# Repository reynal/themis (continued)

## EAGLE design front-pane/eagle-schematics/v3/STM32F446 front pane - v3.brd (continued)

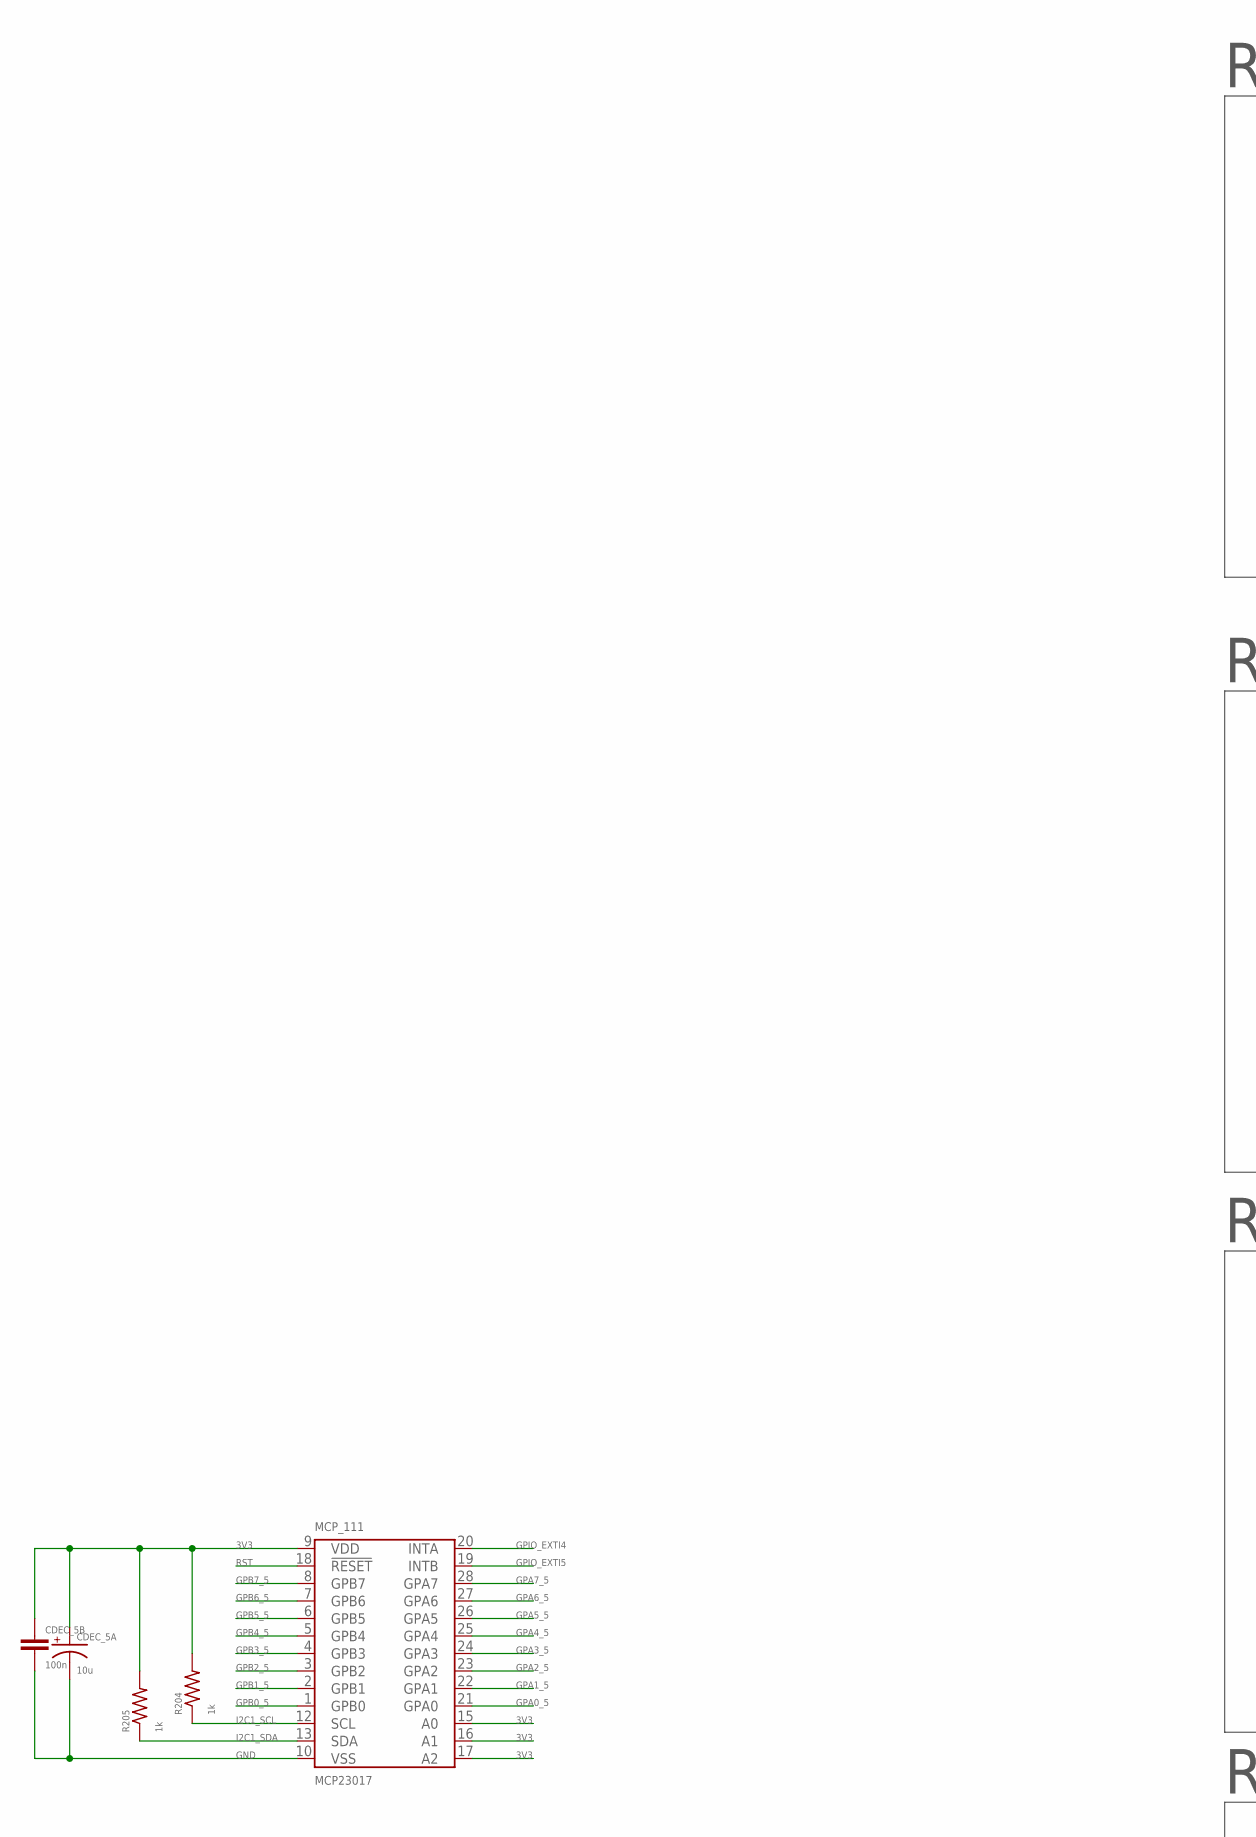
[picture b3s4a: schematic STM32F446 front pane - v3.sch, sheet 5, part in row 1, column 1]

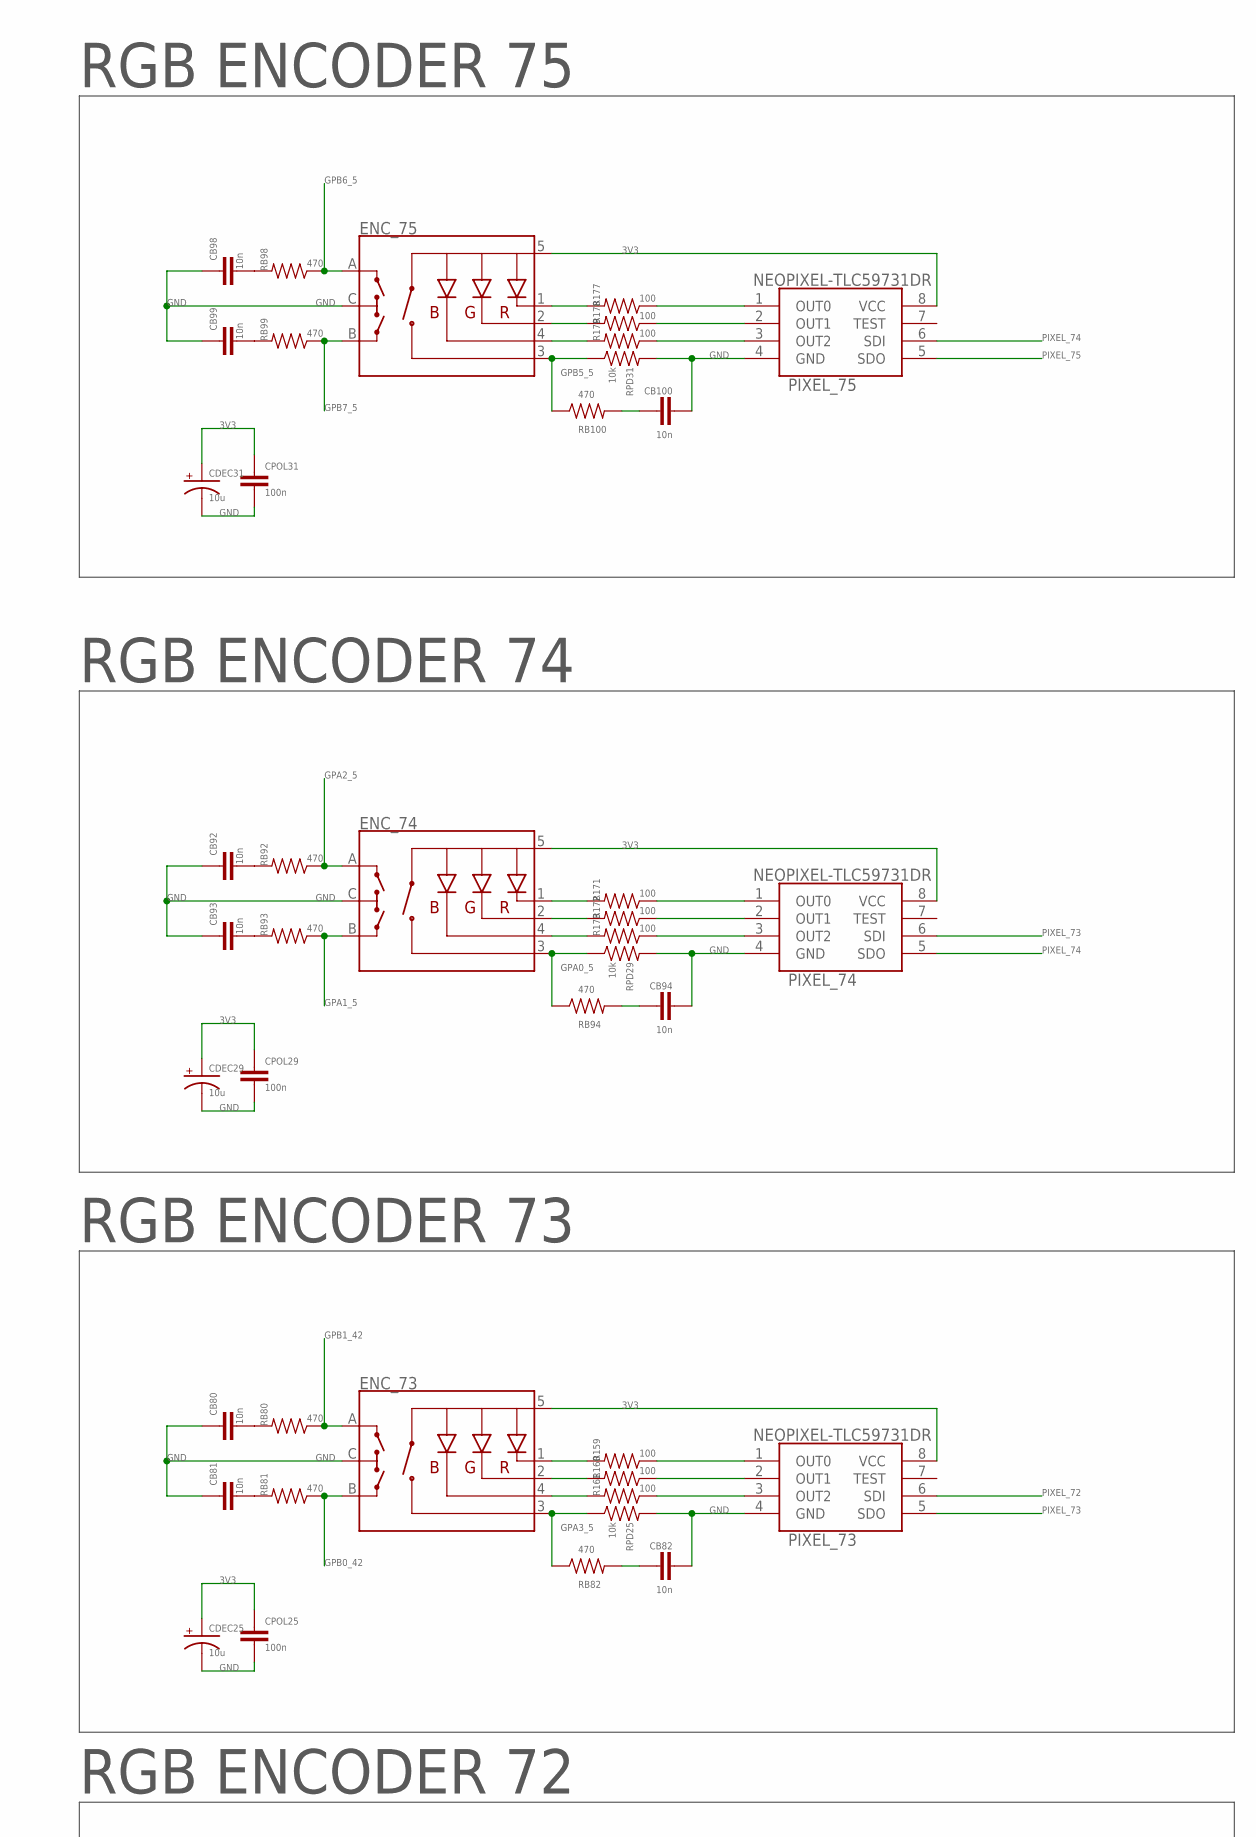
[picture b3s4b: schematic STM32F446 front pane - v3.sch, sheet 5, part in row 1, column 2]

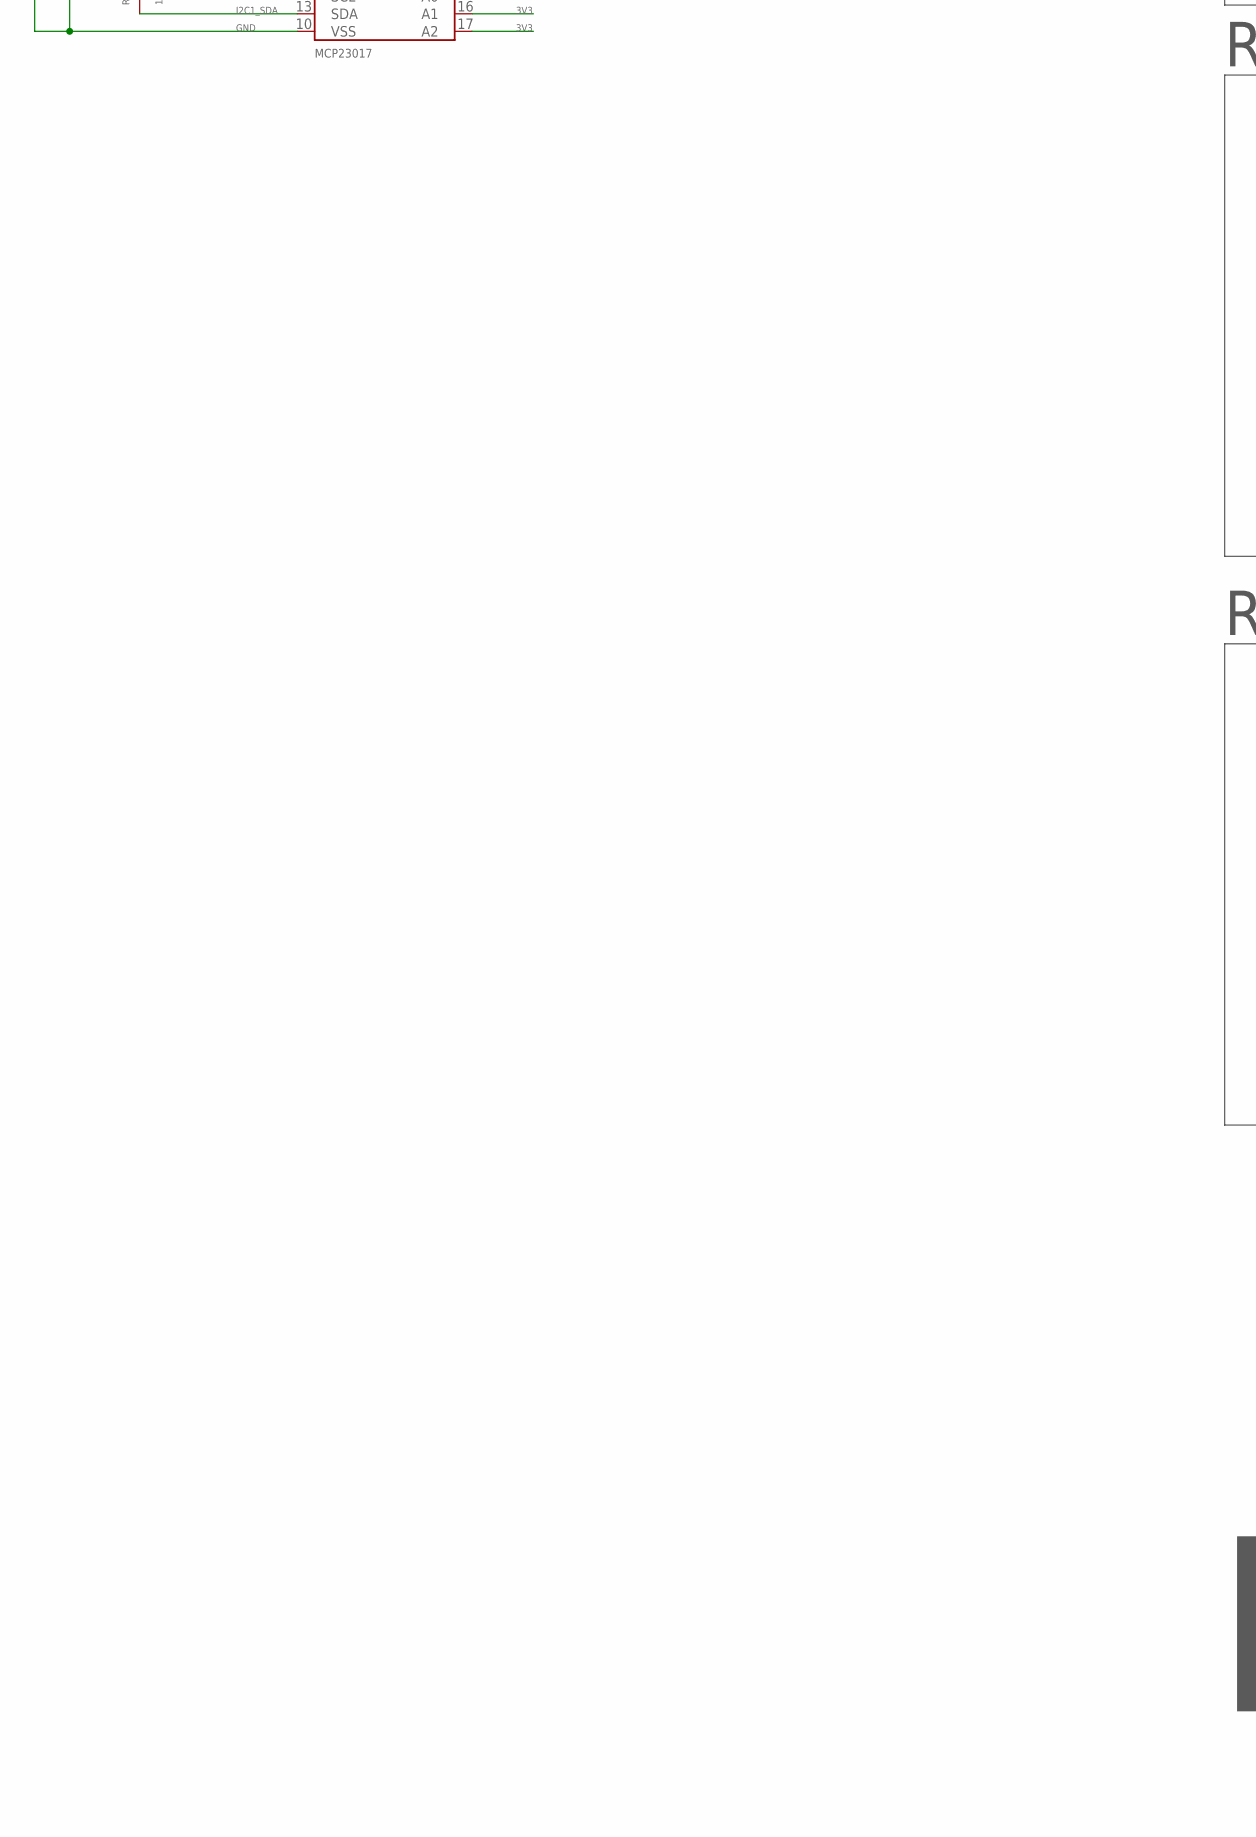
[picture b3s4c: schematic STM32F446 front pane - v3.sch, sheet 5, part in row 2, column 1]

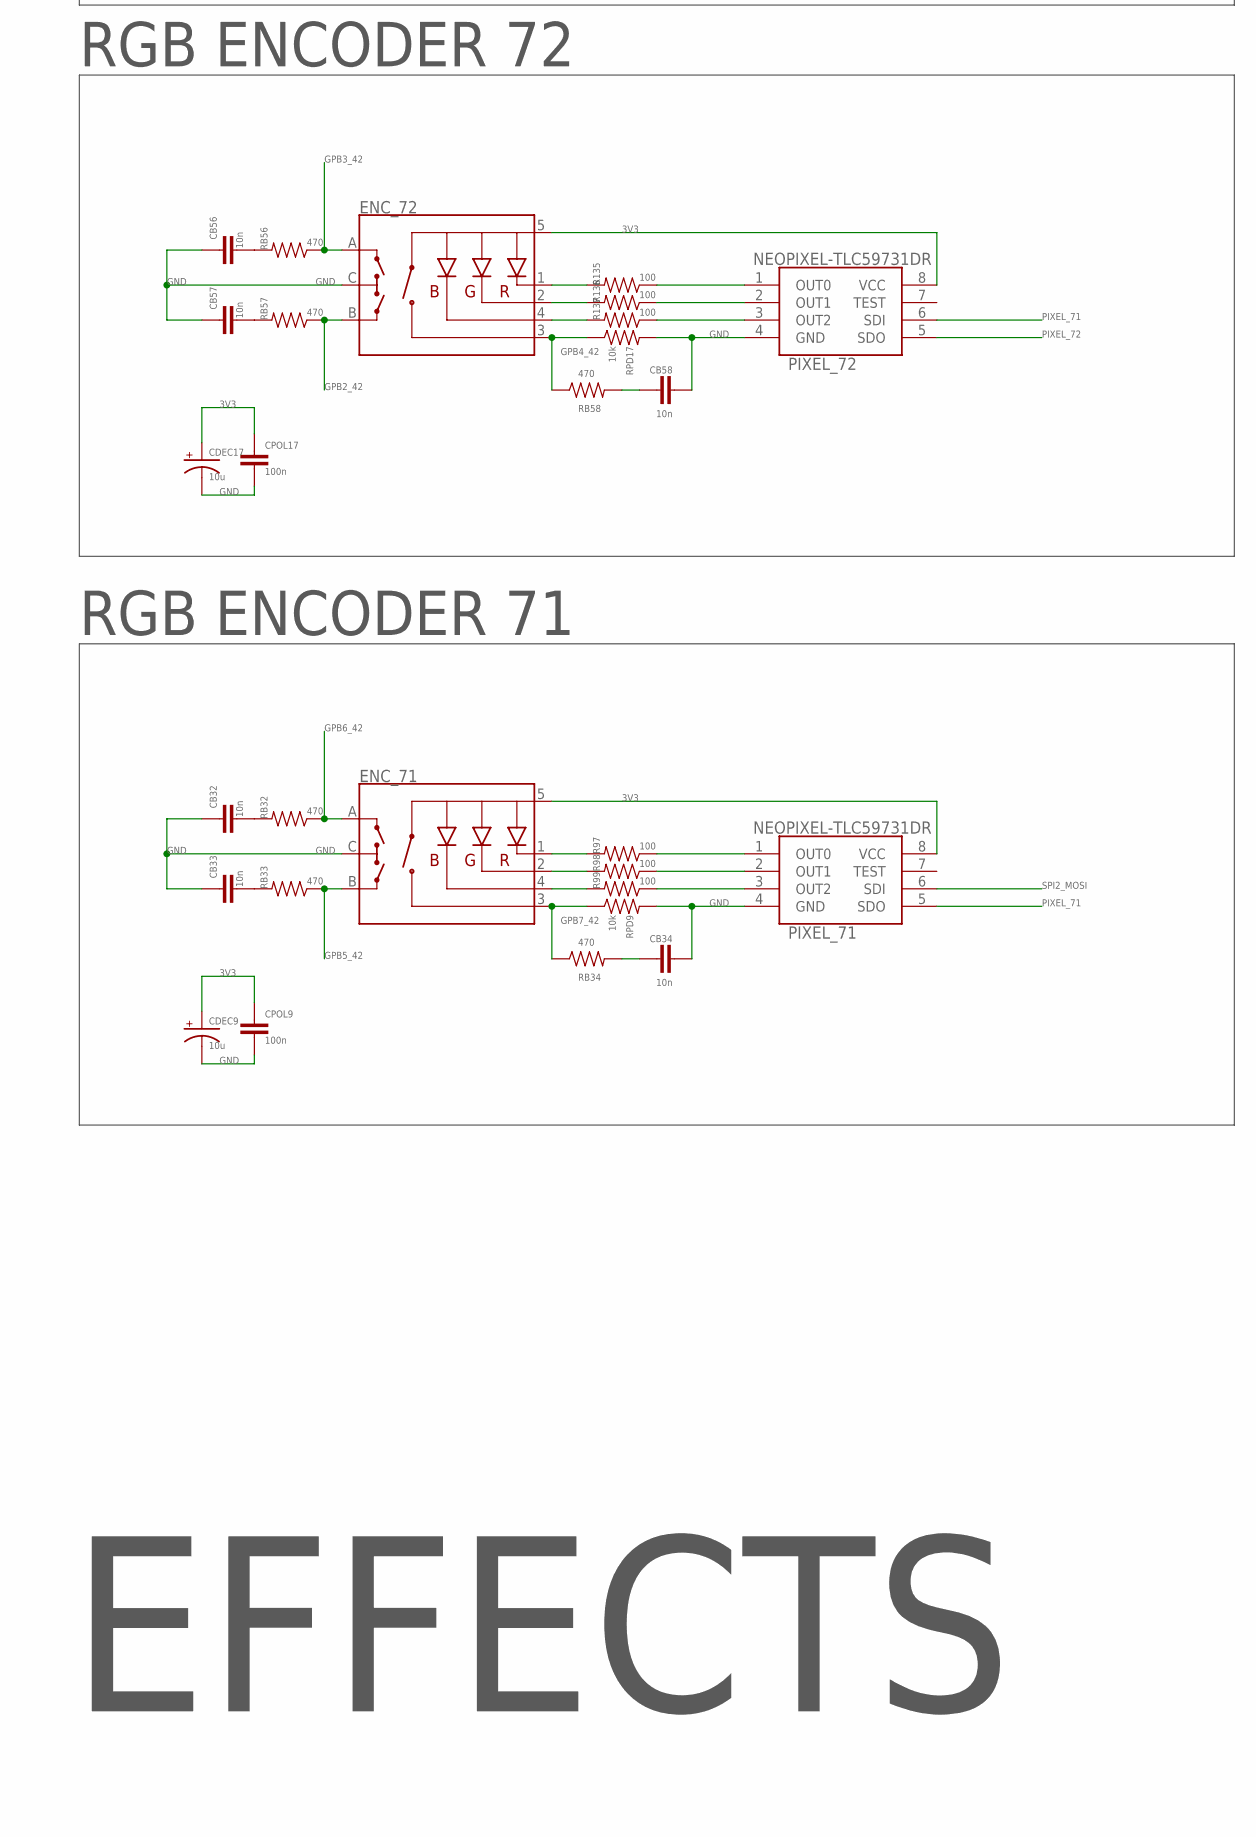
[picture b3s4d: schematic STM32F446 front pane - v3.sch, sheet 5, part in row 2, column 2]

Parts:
CB32, CB33, CB34, CB56, CB57, CB58, CB80, CB81, CB82, CB92, CB93, CB94, CB98, CB99, CB100: 10n; 0805-CAP
CDEC9, CDEC17, CDEC25, CDEC29, CDEC31: 10u; CPOL2917
CDEC_5A: 10u; CPOL2917
CDEC_5B: 100n; 0805-CAP
CPOL9, CPOL17, CPOL25, CPOL29, CPOL31: 100n; 0805-CAP
ENC_71, ENC_72, ENC_73, ENC_74, ENC_75: ENCODER-RGB-SWITCH-NO_NUT; ENCODER_LED_3
MCP_111: MCP23017; SOIC-28
PIXEL_71, PIXEL_72, PIXEL_73, PIXEL_74, PIXEL_75: NEOPIXEL-TLC59731DR; SOIC127P600X175-8N
R97, R98, R99, R135, R136, R137, R159, R160, R161, R171, R172, R173, R177, R178, R179: 100; 1206
R204, R205: 1k; R0805
RB32, RB33, RB34, RB56, RB57, RB58, RB80, RB81, RB82, RB92, RB93, RB94, RB98, RB99, RB100: 470; 1206
RPD9, RPD17, RPD25, RPD29, RPD31: 10k; 1206

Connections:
3V3: CDEC9.+, CDEC17.+, CDEC25.+, CDEC29.+, CDEC31.+, CDEC_5A.+, CDEC_5B.1, CPOL9.1, CPOL17.1, CPOL25.1, CPOL29.1, CPOL31.1, ENC_71.5 (+), ENC_72.5 (+), ENC_73.5 (+), ENC_74.5 (+), ENC_75.5 (+), MCP_111.9 (VDD), MCP_111.15 (A0), MCP_111.16 (A1), MCP_111.17 (A2), PIXEL_71.8 (VCC), PIXEL_72.8 (VCC), PIXEL_73.8 (VCC), PIXEL_74.8 (VCC), PIXEL_75.8 (VCC), R204.2, R205.2; also elsewhere on the board
GND: CB32.1, CB33.1, CB34.2, CB56.1, CB57.1, CB58.2, CB80.1, CB81.1, CB82.2, CB92.1, CB93.1, CB94.2, CB98.1, CB99.1, CB100.2, CDEC9.-, CDEC17.-, CDEC25.-, CDEC29.-, CDEC31.-, CDEC_5A.-, CDEC_5B.2, CPOL9.2, CPOL17.2, CPOL25.2, CPOL29.2, CPOL31.2, ENC_71.C, ENC_72.C, ENC_73.C, ENC_74.C, ENC_75.C, MCP_111.10 (VSS), PIXEL_71.4 (GND), PIXEL_72.4 (GND), PIXEL_73.4 (GND), PIXEL_74.4 (GND), PIXEL_75.4 (GND), RPD9.2, RPD17.2, RPD25.2, RPD29.2, RPD31.2; also elsewhere on the board
GPA0_5: ENC_74.3 (SW), MCP_111.21 (GPA0), RB94.1, RPD29.1
GPA1_5: ENC_74.B, MCP_111.22 (GPA1), RB93.1
GPA2_5: ENC_74.A, MCP_111.23 (GPA2), RB92.1
GPA3_5: ENC_73.3 (SW), MCP_111.24 (GPA3), RB82.1, RPD25.1
GPA4_5: MCP_111.25 (GPA4); also elsewhere on the board
GPA5_5: MCP_111.26 (GPA5); also elsewhere on the board
GPA6_5: MCP_111.27 (GPA6); also elsewhere on the board
GPA7_5: MCP_111.28 (GPA7); also elsewhere on the board
GPB0_5: MCP_111.1 (GPB0); also elsewhere on the board
GPB0_42: ENC_73.B, RB81.1; also elsewhere on the board
GPB1_5: MCP_111.2 (GPB1); also elsewhere on the board
GPB1_42: ENC_73.A, RB80.1; also elsewhere on the board
GPB2_5: MCP_111.3 (GPB2); also elsewhere on the board
GPB2_42: ENC_72.B, RB57.1; also elsewhere on the board
GPB3_5: MCP_111.4 (GPB3); also elsewhere on the board
GPB3_42: ENC_72.A, RB56.1; also elsewhere on the board
GPB4_5: MCP_111.5 (GPB4); also elsewhere on the board
GPB4_42: ENC_72.3 (SW), RB58.1, RPD17.1; also elsewhere on the board
GPB5_5: ENC_75.3 (SW), MCP_111.6 (GPB5), RB100.1, RPD31.1
GPB5_42: ENC_71.B, RB33.1; also elsewhere on the board
GPB6_5: ENC_75.A, MCP_111.7 (GPB6), RB98.1
GPB6_42: ENC_71.A, RB32.1; also elsewhere on the board
GPB7_5: ENC_75.B, MCP_111.8 (GPB7), RB99.1
GPB7_42: ENC_71.3 (SW), RB34.1, RPD9.1; also elsewhere on the board
GPIO_EXTI4: MCP_111.20 (INTA); also elsewhere on the board
GPIO_EXTI5: MCP_111.19 (INTB); also elsewhere on the board
I2C1_SCL: MCP_111.12 (SCL), R204.1; also elsewhere on the board
I2C1_SDA: MCP_111.13 (SDA), R205.1; also elsewhere on the board
unnamed: ENC_71.1 (-R), R97.2
unnamed: ENC_71.2 (-G), R98.2
unnamed: ENC_71.4 (-B), R99.2
unnamed: PIXEL_71.1 (OUT0), R97.1
unnamed: PIXEL_71.2 (OUT1), R98.1
unnamed: PIXEL_71.3 (OUT2), R99.1
unnamed: CB32.2, RB32.2
unnamed: CB33.2, RB33.2
unnamed: CB34.1, RB34.2
unnamed: ENC_72.1 (-R), R135.2
unnamed: ENC_72.2 (-G), R136.2
unnamed: ENC_72.4 (-B), R137.2
unnamed: PIXEL_72.1 (OUT0), R135.1
unnamed: PIXEL_72.2 (OUT1), R136.1
unnamed: PIXEL_72.3 (OUT2), R137.1
unnamed: CB56.2, RB56.2
unnamed: CB57.2, RB57.2
unnamed: CB58.1, RB58.2
unnamed: ENC_73.1 (-R), R159.2
unnamed: ENC_73.2 (-G), R160.2
unnamed: ENC_73.4 (-B), R161.2
unnamed: PIXEL_73.1 (OUT0), R159.1
unnamed: PIXEL_73.2 (OUT1), R160.1
unnamed: PIXEL_73.3 (OUT2), R161.1
unnamed: CB80.2, RB80.2
unnamed: CB81.2, RB81.2
unnamed: CB82.1, RB82.2
unnamed: ENC_74.1 (-R), R171.2
unnamed: ENC_74.2 (-G), R172.2
unnamed: ENC_74.4 (-B), R173.2
unnamed: PIXEL_74.1 (OUT0), R171.1
unnamed: PIXEL_74.2 (OUT1), R172.1
unnamed: PIXEL_74.3 (OUT2), R173.1
unnamed: CB92.2, RB92.2
unnamed: CB93.2, RB93.2
unnamed: CB94.1, RB94.2
unnamed: ENC_75.1 (-R), R177.2
unnamed: ENC_75.2 (-G), R178.2
unnamed: ENC_75.4 (-B), R179.2
unnamed: PIXEL_75.1 (OUT0), R177.1
unnamed: PIXEL_75.2 (OUT1), R178.1
unnamed: PIXEL_75.3 (OUT2), R179.1
unnamed: CB98.2, RB98.2
unnamed: CB99.2, RB99.2
unnamed: CB100.1, RB100.2
PIXEL_71: PIXEL_71.5 (SDO), PIXEL_72.6 (SDI)
PIXEL_72: PIXEL_72.5 (SDO), PIXEL_73.6 (SDI)
PIXEL_73: PIXEL_73.5 (SDO), PIXEL_74.6 (SDI)
PIXEL_74: PIXEL_74.5 (SDO), PIXEL_75.6 (SDI)
PIXEL_75: PIXEL_75.5 (SDO); also elsewhere on the board
RST: MCP_111.18 (!RESET); also elsewhere on the board
SPI2_MOSI: PIXEL_71.6 (SDI); also elsewhere on the board

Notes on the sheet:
EFFECTS
RGB ENCODER 71
RGB ENCODER 72
RGB ENCODER 73
RGB ENCODER 74
RGB ENCODER 75

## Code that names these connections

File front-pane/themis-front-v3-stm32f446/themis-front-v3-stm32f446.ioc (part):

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Mcu.Name=STM32F446R(C-E)Tx
Mcu.Package=LQFP64
Mcu.UserName=STM32F446RCTx
PA0-WKUP.Mode=Asynchronous
PA0-WKUP.Signal=UART4_TX
PA1.Signal=ADCx_IN1
PA10.GPIOParameters=GPIO_PuPd,GPIO_Label,GPIO_ModeDefaultEXTI
PA10.GPIO_Label=MCP_001_INTB
PA10.GPIO_ModeDefaultEXTI=GPIO_MODE_IT_FALLING
PA10.GPIO_PuPd=GPIO_PULLUP
PA10.Signal=GPXTI10
PA11.GPIOParameters=GPIO_PuPd,GPIO_Label,GPIO_ModeDefaultEXTI
PA11.GPIO_Label=MCP_000_INTB
PA11.GPIO_ModeDefaultEXTI=GPIO_MODE_IT_FALLING
PA11.GPIO_PuPd=GPIO_PULLUP
PA11.Signal=GPXTI11
PA12.GPIOParameters=GPIO_PuPd,GPIO_Label,GPIO_ModeDefaultEXTI
PA12.GPIO_Label=MCP_000_INTA
PA12.GPIO_ModeDefaultEXTI=GPIO_MODE_IT_FALLING
PA12.GPIO_PuPd=GPIO_PULLUP
PA12.Signal=GPXTI12
PA13.Mode=Serial_Wire
PA13.Signal=SYS_JTMS-SWDIO
PA14.Mode=Serial_Wire
PA14.Signal=SYS_JTCK-SWCLK
PA2.GPIOParameters=GPIO_Label
PA2.GPIO_Label=U2_TX
PA2.Signal=GPIO_Output
PA3.GPIOParameters=GPIO_Label
PA3.GPIO_Label=U2_RX
PA3.Signal=GPIO_Output
PA4.Signal=ADCx_IN4
PA5.Mode=TX_Only_Simplex_Unidirect_Master
PA5.Signal=SPI1_SCK
PA6.Signal=S_TIM3_CH1
PA7.Mode=TX_Only_Simplex_Unidirect_Master
PA7.Signal=SPI1_MOSI
PA8.GPIOParameters=GPIO_Pu
PA8.GPIO_Pu=GPIO_PULLUP
PA8.Mode=I2C
PA8.Signal=I2C3_SCL
PA9.GPIOParameters=GPIO_PuPd,GPIO_Label,GPIO_ModeDefaultEXTI
PA9.GPIO_Label=MCP_001_INTA
PA9.GPIO_ModeDefaultEXTI=GPIO_MODE_IT_FALLING
PA9.GPIO_PuPd=GPIO_PULLUP
PA9.Signal=GPXTI9
PB0.Mode=TX_Only_Simplex_Unidirect_Master
PB0.Signal=SPI3_MOSI
PB1.GPIOParameters=GPIO_PuPd,GPIO_Label,GPIO_ModeDefaultEXTI
PB1.GPIO_Label=MCP_011_INTB
PB1.GPIO_ModeDefaultEXTI=GPIO_MODE_IT_FALLING
PB1.GPIO_PuPd=GPIO_PULLUP
PB1.Signal=GPXTI1
PB10.GPIOParameters=GPIO_Pu
PB10.GPIO_Pu=GPIO_PULLUP
PB10.Mode=I2C
PB10.Signal=I2C2_SCL
PB13.Mode=TX_Only_Simplex_Unidirect_Master
PB13.Signal=SPI2_SCK
PB14.GPIOParameters=GPIO_PuPd,GPIO_Label,GPIO_ModeDefaultEXTI
PB14.GPIO_Label=MCP_011_INTA
PB14.GPIO_ModeDefaultEXTI=GPIO_MODE_IT_FALLING
PB14.GPIO_PuPd=GPIO_PULLUP
PB14.Signal=GPXTI14
PB15.GPIOParameters=GPIO_PuPd,GPIO_Label,GPIO_ModeDefaultEXTI
PB15.GPIO_Label=MCP_100_INTA
PB15.GPIO_ModeDefaultEXTI=GPIO_MODE_IT_FALLING
PB15.GPIO_PuPd=GPIO_PULLUP
PB15.Signal=GPXTI15
PB3.GPIOParameters=GPIO_Label
PB3.GPIO_Label=MCP_RST
PB3.Signal=GPIO_Output
PB6.Mode=Asynchronous
PB6.Signal=USART1_TX
PB7.Mode=Asynchronous
PB7.Signal=USART1_RX
PB8.GPIOParameters=GPIO_Pu
PB8.GPIO_Pu=GPIO_PULLUP
PB8.Mode=I2C
PB8.Signal=I2C1_SCL
PB9.GPIOParameters=GPIO_Pu
PB9.GPIO_Pu=GPIO_PULLUP
PB9.Mode=I2C
PB9.Signal=I2C1_SDA
PC0.Signal=ADCx_IN10
PC1.Mode=TX_Only_Simplex_Unidirect_Master
PC1.Signal=SPI2_MOSI
PC10.Mode=TX_Only_Simplex_Unidirect_Master
PC10.Signal=SPI3_SCK
PC11.Mode=Asynchronous
PC11.Signal=UART4_RX
PC12.GPIOParameters=GPIO_Pu
PC12.GPIO_Pu=GPIO_PULLUP
PC12.Mode=I2C
PC12.Signal=I2C2_SDA
PC13.GPIOParameters=GPIO_PuPd,GPIO_Label,GPIO_ModeDefaultEXTI
PC13.GPIO_Label=MCP_101_INTA
PC13.GPIO_ModeDefaultEXTI=GPIO_MODE_IT_FALLING
PC13.GPIO_PuPd=GPIO_PULLUP
PC13.Signal=GPXTI13
PC2.GPIOParameters=GPIO_PuPd,GPIO_Label,GPIO_ModeDefaultEXTI
PC2.GPIO_Label=MCP_110_INTB
PC2.GPIO_ModeDefaultEXTI=GPIO_MODE_IT_FALLING
PC2.GPIO_PuPd=GPIO_PULLUP
PC2.Signal=GPXTI2
PC3.GPIOParameters=GPIO_PuPd,GPIO_Label,GPIO_ModeDefaultEXTI
PC3.GPIO_Label=MCP_110_INTA
PC3.GPIO_ModeDefaultEXTI=GPIO_MODE_IT_FALLING
PC3.GPIO_PuPd=GPIO_PULLUP
PC3.Signal=GPXTI3
PC4.GPIOParameters=GPIO_PuPd,GPIO_Label,GPIO_ModeDefaultEXTI
PC4.GPIO_Label=MCP_111_INTA
PC4.GPIO_ModeDefaultEXTI=GPIO_MODE_IT_FALLING
PC4.GPIO_PuPd=GPIO_PULLUP
PC4.Signal=GPXTI4
PC5.GPIOParameters=GPIO_PuPd,GPIO_Label,GPIO_ModeDefaultEXTI
PC5.GPIO_Label=MCP_111_INTB
PC5.GPIO_ModeDefaultEXTI=GPIO_MODE_IT_FALLING
PC5.GPIO_PuPd=GPIO_PULLUP
PC5.Signal=GPXTI5
PC6.GPIOParameters=GPIO_PuPd,GPIO_Label,GPIO_ModeDefaultEXTI
PC6.GPIO_Label=MCP_100_INTB
PC6.GPIO_ModeDefaultEXTI=GPIO_MODE_IT_FALLING
PC6.GPIO_PuPd=GPIO_PULLUP
PC6.Signal=GPXTI6
PC7.GPIOParameters=GPIO_PuPd,GPIO_Label,GPIO_ModeDefaultEXTI
PC7.GPIO_Label=MCP_010_INTA
PC7.GPIO_ModeDefaultEXTI=GPIO_MODE_IT_FALLING
PC7.GPIO_PuPd=GPIO_PULLUP
PC7.Signal=GPXTI7
PC8.GPIOParameters=GPIO_PuPd,GPIO_Label,GPIO_ModeDefaultEXTI
PC8.GPIO_Label=MCP_010_INTB
PC8.GPIO_ModeDefaultEXTI=GPIO_MODE_IT_FALLING
PC8.GPIO_PuPd=GPIO_PULLUP
PC8.Signal=GPXTI8
PC9.GPIOParameters=GPIO_Pu
PC9.GPIO_Pu=GPIO_PULLUP
PC9.Mode=I2C
PC9.Signal=I2C3_SDA
PH0-OSC_IN.GPIOParameters=GPIO_PuPd,GPIO_Label,GPIO_ModeDefaultEXTI
PH0-OSC_IN.GPIO_Label=MCP_101_INTB
PH0-OSC_IN.GPIO_ModeDefaultEXTI=GPIO_MODE_IT_FALLING
PH0-OSC_IN.GPIO_PuPd=GPIO_PULLUP
PH0-OSC_IN.Signal=GPXTI0
RCC.SYSCLKFreq_VALUE=180000000
RCC.SYSCLKSource=RCC_SYSCLKSOURCE_PLLCLK
board=custom

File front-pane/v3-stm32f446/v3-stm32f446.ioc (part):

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Mcu.UserName=STM32F446RCTx
PB10.Mode=I2C
PC10.Signal=SPI3_SCK
PC12.Signal=I2C2_SDA
PB13.Signal=SPI2_SCK
PB15.Signal=GPXTI15
RCC.SYSCLKSource=RCC_SYSCLKSOURCE_PLLCLK
PA12.Signal=GPXTI12
PB6.Signal=USART1_TX
PC7.Signal=GPXTI7
PB6.Mode=Asynchronous
PC3.Signal=GPXTI3
PA14.Mode=Serial_Wire
PC9.Mode=I2C
PB3.GPIOParameters=GPIO_Label
PB7.Signal=USART1_RX
PA8.Signal=I2C3_SCL
Mcu.Package=LQFP64
PB9.Signal=I2C1_SDA
PB1.Signal=GPXTI1
PA6.Signal=S_TIM3_CH1
PA10.Signal=GPXTI10
PC11.Mode=Asynchronous
PC5.Signal=GPXTI5
PB13.Mode=TX_Only_Simplex_Unidirect_Master
PA3.Signal=USART2_RX
PA5.Mode=TX_Only_Simplex_Unidirect_Master
PB3.GPIO_Label=MCP_RST
PA7.Mode=TX_Only_Simplex_Unidirect_Master
PC11.Signal=UART4_RX
PC8.Signal=GPXTI8
PC2.Signal=GPXTI2
PC4.Signal=GPXTI4
PC6.Signal=GPXTI6
PC10.Mode=TX_Only_Simplex_Unidirect_Master
PC0.Signal=ADCx_IN10
PA0-WKUP.Signal=UART4_TX
PA0-WKUP.Mode=Asynchronous
PA13.Signal=SYS_JTMS-SWDIO
PA3.Mode=Asynchronous
PB9.Mode=I2C
PA9.Signal=GPXTI9
PA1.Signal=ADCx_IN1
PB10.Signal=I2C2_SCL
PB14.Signal=GPXTI14
PA5.Signal=SPI1_SCK
PC12.Mode=I2C
PB0.Mode=TX_Only_Simplex_Unidirect_Master
board=custom
PA13.Mode=Serial_Wire
Mcu.Name=STM32F446R(C-E)Tx
PA2.Signal=USART2_TX
PB3.Signal=GPIO_Output
PA4.Signal=ADCx_IN4
RCC.SYSCLKFreq_VALUE=180000000
PB7.Mode=Asynchronous
PA11.Signal=GPXTI11
PA14.Signal=SYS_JTCK-SWCLK
PB8.Mode=I2C
PA2.Mode=Asynchronous
PB8.Signal=I2C1_SCL
PA8.Mode=I2C
PC9.Signal=I2C3_SDA
PB0.Signal=SPI3_MOSI
PC1.Signal=SPI2_MOSI
PC1.Mode=TX_Only_Simplex_Unidirect_Master
PA7.Signal=SPI1_MOSI

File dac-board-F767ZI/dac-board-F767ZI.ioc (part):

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Mcu.Name=STM32F767ZITx
Mcu.Package=LQFP144
Mcu.UserName=STM32F767ZITx
PA0/WKUP.Signal=S_TIM2_CH1_ETR
PA1.GPIOParameters=GPIO_Label
PA1.GPIO_Label=RMII_REF_CLK [LAN8742A-CZ-TR_REFCLK0]
PA1.Signal=ETH_REF_CLK
PA10.GPIOParameters=GPIO_Label
PA10.GPIO_Label=USB_ID
PA10.Signal=USB_OTG_FS_ID
PA11.GPIOParameters=GPIO_Label
PA11.GPIO_Label=USB_DM
PA11.Signal=USB_OTG_FS_DM
PA12.GPIOParameters=GPIO_Label
PA12.GPIO_Label=USB_DP
PA12.Signal=USB_OTG_FS_DP
PA13.GPIOParameters=GPIO_Label
PA13.GPIO_Label=TMS
PA13.Signal=SYS_JTMS-SWDIO
PA14.GPIOParameters=GPIO_Label
PA14.GPIO_Label=TCK
PA14.Signal=SYS_JTCK-SWCLK
PA2.GPIOParameters=GPIO_Label
PA2.GPIO_Label=RMII_MDIO [LAN8742A-CZ-TR_MDIO]
PA2.Signal=ETH_MDIO
PA3.Signal=S_TIM2_CH4
PA7.GPIOParameters=GPIO_Label
PA7.GPIO_Label=RMII_CRS_DV [LAN8742A-CZ-TR_CRS_DV]
PA7.Signal=ETH_CRS_DV
PA8.GPIOParameters=GPIO_Label
PA8.GPIO_Label=USB_SOF [TP1]
PA8.Signal=USB_OTG_FS_SOF
PA9.GPIOParameters=GPIO_Label
PA9.GPIO_Label=USB_VBUS
PA9.Signal=USB_OTG_FS_VBUS
PB10.Signal=S_TIM2_CH3
PB12.Mode=Asynchronous
PB12.Signal=UART5_RX
PB13.GPIOParameters=GPIO_Label
PB13.GPIO_Label=RMII_TXD1 [LAN8742A-CZ-TR_TXD1]
PB13.Signal=ETH_TXD1
PB14.GPIOParameters=GPIO_Label
PB14.GPIO_Label=LD3 [Red]
PB14.Signal=GPIO_Output
PB2.Mode=RX_Only_Simplex_Unidirect_Slave
PB2.Signal=SPI3_MOSI
PB3.GPIOParameters=GPIO_Label
PB3.GPIO_Label=SW0
PB3.Signal=SYS_JTDO-SWO
PB6.Mode=I2C
PB6.Signal=I2C1_SCL
PB7.GPIOParameters=GPIO_Label
PB7.GPIO_Label=LD2 [Blue]
PB7.Signal=GPIO_Output
PB9.Mode=I2C
PB9.Signal=I2C1_SDA
PC1.GPIOParameters=GPIO_Label
PC1.GPIO_Label=RMII_MDC [LAN8742A-CZ-TR_MDC]
PC1.Signal=ETH_MDC
PC10.Mode=RX_Only_Simplex_Unidirect_Slave
PC10.Signal=SPI3_SCK
PC11.GPIOParameters=GPIO_Speed,GPIO_Label
PC11.GPIO_Label=LS138_A2
PC11.GPIO_Speed=GPIO_SPEED_FREQ_HIGH
PC11.Signal=GPIO_Output
PC12.Mode=Asynchronous
PC12.Signal=UART5_TX
PC13.GPIOParameters=GPIO_PuPd,GPIO_Label,GPIO_ModeDefaultEXTI
PC13.GPIO_Label=USER_Btn [B1]
PC13.GPIO_ModeDefaultEXTI=GPIO_MODE_IT_RISING_FALLING
PC13.GPIO_PuPd=GPIO_NOPULL
PC13.Signal=GPXTI13
PC14/OSC32_IN.Signal=RCC_OSC32_IN
PC15/OSC32_OUT.Signal=RCC_OSC32_OUT
PC4.GPIOParameters=GPIO_Label
PC4.GPIO_Label=RMII_RXD0 [LAN8742A-CZ-TR_RXD0]
PC4.Signal=ETH_RXD0
PC5.GPIOParameters=GPIO_Label
PC5.GPIO_Label=RMII_RXD1 [LAN8742A-CZ-TR_RXD1]
PC5.Signal=ETH_RXD1
PC6.GPIOParameters=GPIO_PuPd,GPIO_Label,GPIO_ModeDefaultEXTI
PC6.GPIO_Label=CE_RPi
PC6.GPIO_ModeDefaultEXTI=GPIO_MODE_IT_FALLING
PC6.GPIO_PuPd=GPIO_PULLUP
PC6.Signal=GPXTI6
PC8.GPIOParameters=GPIO_Speed,GPIO_Label
PC8.GPIO_Label=LS138_A0
PC8.GPIO_Speed=GPIO_SPEED_FREQ_HIGH
PC8.Signal=GPIO_Output
PC9.GPIOParameters=GPIO_Speed,GPIO_Label
PC9.GPIO_Label=LS138_A1
PC9.GPIO_Speed=GPIO_SPEED_FREQ_HIGH
PC9.Signal=GPIO_Output
PD0.GPIOParameters=GPIO_Label
PD0.GPIO_Label=PULSE_3340
PD0.Signal=GPIO_Output
PD1.GPIOParameters=GPIO_Label
PD1.GPIO_Label=DRUM_SNARE
PD1.Signal=GPIO_Output
PD8.GPIOParameters=GPIO_Label
PD8.GPIO_Label=STLK_RX [STM32F103CBT6_PA3]
PD8.Mode=Asynchronous
PD8.Signal=USART3_TX
PD9.GPIOParameters=GPIO_Label
PD9.GPIO_Label=STLK_TX [STM32F103CBT6_PA2]
PD9.Mode=Asynchronous
PD9.Signal=USART3_RX
PE2.GPIOParameters=GPIO_Label
PE2.GPIO_Label=VCF_4THORDER
PE2.Signal=GPIO_Output
PE4.GPIOParameters=GPIO_Label
PE4.GPIO_Label=VCF_2NDORDER
PE4.Signal=GPIO_Output
PE5.GPIOParameters=GPIO_Label
PE5.GPIO_Label=DRUM_KICK
PE5.Signal=GPIO_Output
PE6.GPIOParameters=GPIO_Label
PE6.GPIO_Label=TRI_3340
PE6.Signal=GPIO_Output
PF0.GPIOParameters=GPIO_Label
PF0.GPIO_Label=DRUM_RIM
PF0.Signal=GPIO_Output
PF1.GPIOParameters=GPIO_Label
PF1.GPIO_Label=DRUM_LOWTOM
PF1.Signal=GPIO_Output
PF2.GPIOParameters=GPIO_Label
PF2.GPIO_Label=DRUM_HIGHTOM
PF2.Signal=GPIO_Output
PF7.Mode=TX_Only_Simplex_Unidirect_Master
PF7.Signal=SPI5_SCK
PF9.Mode=TX_Only_Simplex_Unidirect_Master
PF9.Signal=SPI5_MOSI
PG0.GPIOParameters=GPIO_Speed,GPIO_Label
PG0.GPIO_Label=DAC_CS
PG0.GPIO_Speed=GPIO_SPEED_FREQ_HIGH
PG0.Signal=GPIO_Output
PG11.GPIOParameters=GPIO_Label
PG11.GPIO_Label=RMII_TX_EN [LAN8742A-CZ-TR_TXEN]
PG11.Signal=ETH_TX_EN
PG12.GPIOParameters=GPIO_Label
PG12.GPIO_Label=SYNC_3340
PG12.Signal=GPIO_Output
PG13.GPIOParameters=GPIO_Label
PG13.GPIO_Label=RMII_TXD0 [LAN8742A-CZ-TR_TXD0]
PG13.Signal=ETH_TXD0
PG6.GPIOParameters=GPIO_Speed,GPIO_Label
PG6.GPIO_Label=USB_PowerSwitchOn [STMPS2151STR_EN]
PG6.GPIO_Speed=GPIO_SPEED_FREQ_MEDIUM
PG6.Signal=GPIO_Output
PG7.GPIOParameters=GPIO_Label
PG7.GPIO_Label=USB_OverCurrent [STMPS2151STR_FAULT]
PG7.Signal=GPIO_Input
PG9.GPIOParameters=GPIO_Label
PG9.GPIO_Label=SAW_3340
PG9.Signal=GPIO_Output
PH0/OSC_IN.GPIOParameters=GPIO_Label
PH0/OSC_IN.GPIO_Label=MCO [STM32F103CBT6_PA8]
PH0/OSC_IN.Mode=HSE-External-Oscillator
PH0/OSC_IN.Signal=RCC_OSC_IN
PH1/OSC_OUT.Mode=HSE-External-Oscillator
PH1/OSC_OUT.Signal=RCC_OSC_OUT
RCC.HSE_VALUE=16000000
RCC.SYSCLKFreq_VALUE=216000000
RCC.SYSCLKSource=RCC_SYSCLKSOURCE_PLLCLK
RCC.SYSCLKSourceVirtual=RCC_SYSCLKSOURCE_PLLCLK
board=NUCLEO-F767ZI
boardIOC=true

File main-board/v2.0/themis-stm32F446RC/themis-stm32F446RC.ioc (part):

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Mcu.Name=STM32F446R(C-E)Tx
Mcu.Package=LQFP64
Mcu.UserName=STM32F446RCTx
PA0-WKUP.Signal=S_TIM2_CH1_ETR
PA1.Signal=S_TIM2_CH2
PA13.Mode=Serial_Wire
PA13.Signal=SYS_JTMS-SWDIO
PA14.Mode=Serial_Wire
PA14.Signal=SYS_JTCK-SWCLK
PA15.GPIOParameters=GPIO_Label
PA15.GPIO_Label=EXTENSION_1
PA15.Signal=GPIO_Output
PA2.Signal=ADCx_IN2
PA3.Signal=ADCx_IN3
PA4.GPIOParameters=GPIO_Speed,PinState,GPIO_Label
PA4.GPIO_Label=BH2221_LD
PA4.GPIO_Speed=GPIO_SPEED_FREQ_HIGH
PA4.PinState=GPIO_PIN_SET
PA4.Signal=GPIO_Output
PA5.Mode=TX_Only_Simplex_Unidirect_Master
PA5.Signal=SPI1_SCK
PA6.GPIOParameters=GPIO_Label
PA6.GPIO_Label=LED_GREEN
PA6.Signal=GPIO_Output
PA7.Mode=TX_Only_Simplex_Unidirect_Master
PA7.Signal=SPI1_MOSI
PB0.Signal=S_TIM3_CH3
PB10.Mode=TX_Only_Simplex_Unidirect_Master
PB10.Signal=SPI2_SCK
PB12.GPIOParameters=GPIO_Speed,PinState,GPIO_Label
PB12.GPIO_Label=AD5644_SYNC
PB12.GPIO_Speed=GPIO_SPEED_FREQ_HIGH
PB12.PinState=GPIO_PIN_SET
PB12.Signal=GPIO_Output
PB6.Mode=Asynchronous
PB6.Signal=USART1_TX
PB7.Mode=Asynchronous
PB7.Signal=USART1_RX
PB8.Mode=I2C
PB8.Signal=I2C1_SCL
PB9.Mode=I2C
PB9.Signal=I2C1_SDA
PC1.Mode=TX_Only_Simplex_Unidirect_Master
PC1.Signal=SPI2_MOSI
PC10.GPIOParameters=GPIO_Label
PC10.GPIO_Label=EXTENSION_2
PC10.Signal=GPIO_Output
PC11.GPIOParameters=GPIO_Label
PC11.GPIO_Label=EXTENSION_3
PC11.Signal=GPIO_Output
PC12.GPIOParameters=GPIO_Label
PC12.GPIO_Label=EXTENSION_4
PC12.Signal=GPIO_Output
PC7.Signal=S_TIM3_CH2
PC8.GPIOParameters=GPIO_Label
PC8.GPIO_Label=SW2
PC8.Signal=GPIO_Input
PC9.GPIOParameters=GPIO_Label
PC9.GPIO_Label=SW1
PC9.Signal=GPIO_Input
PH0-OSC_IN.Mode=HSE-External-Oscillator
PH0-OSC_IN.Signal=RCC_OSC_IN
PH1-OSC_OUT.Mode=HSE-External-Oscillator
PH1-OSC_OUT.Signal=RCC_OSC_OUT
RCC.HSE_VALUE=16000000
RCC.SYSCLKFreq_VALUE=180000000
RCC.SYSCLKSource=RCC_SYSCLKSOURCE_PLLCLK
board=custom

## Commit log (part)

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2018-09-30 Add readme file
2018-10-04 Set theme jekyll-theme-tactile
2018-10-16 First front pane architecture in java
2018-10-23 Changed ADSR model
2018-11-09 added method with new argument
2018-11-09 removed comments
2018-11-13 initial website
2018-11-13 new config
2018-11-13 Set theme jekyll-theme-cayman
2018-11-13 site update
2018-11-13 update site
2018-11-20 Update Bastien
2018-11-22 Removed jekyll
2018-11-27 sequenceur alex
2018-11-27 cleaned warning
2018-12-01 web site update
2018-12-03 Started implementation of IS31FL3731 device
2018-12-04 IS31FL3139
2018-12-05 finalised model architecture
2018-12-20 New article by Morgan
2019-01-24 Sequenceur MIDI
2019-01-24 Model package
2019-01-24 Test and logo modification
2019-01-24 Up fin séance / Début listener
2019-01-28 added model listeners
2019-01-28 Added listeners
2019-01-28 Added SPI transmitter
2019-01-29 Main simulator clean & Midi gesture added
2019-01-29 rm classpath
2019-01-30 Added package model.midi
2019-01-30 Modified Main with UI mode selection
2019-01-30 Lucien's update
2019-01-30 SPI transmitter improvement
2019-01-31 MIDI Implementation + transmission over SPI to STM32
2019-01-31 Merge branch 'master' of https://github.com/reynal/themis.git
    Conflicts:
    RPi/src/application/Main.java
2019-02-07 Java.swing adaptation + main2
2019-02-09 Simplified controller package + optimized Main vs Main2 into JavaFXMain and SwingMain
2019-02-09 Optimized VCO models
2019-02-09 Reorganized view package + created device package + cleaned physical encoder code
2019-02-09 MCP23017 bug fix
2019-02-10 new UI generation code
2019-02-19 Update SpiTransmitter.java
    J'ai mis en commentaire le détail de "value" dans chacun des cas (booléen, double ou enum)
2019-03-04 Improved view architecture
2019-03-06 Created two factories for controls and views
2019-03-08 Improved the whole controller-view architecture
2019-03-10 Created TouchScreenView architecture and default view
2019-03-10 Added constant fields for model labels
2019-03-10 TouchscreenView now integrated into main app
2019-03-10 Cleaned view.touchscreen folder
2019-03-12 Adding views backgrounds and fixing view.touchscreen interface
2019-03-21 View changing menu + SpiTransmitter modification (by Loïc)
2019-03-26 Add files via upload
    Modifs RPi Loic
2019-03-26 Update MenuBar listeners
2019-03-26 MenuBar working w/ 3340
2019-03-27 Change folder name for nucleo code
2019-03-27 Improved SPI architecture
2019-03-28 Struct modifications integration
2019-03-28 Splitted frames
2019-04-02 Models updated
2019-04-02 Updated models
2019-04-02 Added testing code for IS31FL3731
2019-04-02 Added views and modified menus
2019-04-02 Image resources for view
2019-04-02 Update + working and modified menu
2019-04-09 first import F767 source code
2019-04-12 Initial upload of STM32F676ZI code
2019-04-12 removed binaries and updated .gitignore accordingly
2019-04-12 Removed useless folder nucleoF767ZI
2019-04-12 Update ignored globs
2019-04-12 Added spreadsheet showing how pins are used on the STM32F767ZI
2019-04-16 added utilities folder and serial term emulation for MIDI debugging and printf console
2019-04-19 Update serial term utility
2019-04-19 Upgraded STM32 code to STM32CubeMX 5.1.0
2019-04-19 Created a unified Midi CC mapping file
2019-04-19 Upgraded Java FX code
2019-04-19 Documentation du code de calibrage
2019-05-06 PushButton hardware code
2019-09-07 bug fix
2019-09-07 added new project for future L432 board
2019-09-16 Added resources folder containing documentation and simulations
2019-09-23 Added v1 EAGLE schematics
2019-09-23 Improved VCO calibration
2019-09-23 Added front pane Eagle schematics
2019-09-23 Added datasheet for analog ICs
2019-09-23 Added project documentation
2019-09-23 renamed files
2019-10-07 Upgraded whole architecture so as to make event dispatching mechanism more efficient
2019-10-07 Improved SerialTermForThemis utility
2019-10-07 Added support for UART and Logging
2019-10-08 Added a virtual piano keyboard
2019-10-09 Implemented transmit method
2019-10-09 Fixing issue with VCF enveloppes
2019-10-09 Remote Synth Parameter editing through UART using Java is working fine except VCF
2019-11-05 Added some documentation
2019-11-05 New post about unity
2019-11-06 Start of the work on neopixels
2019-11-07 The SPI message can now be generated.
2019-11-12 Documentation projet 2018-2019
2019-11-25 New tests.
2019-11-26 We can light up a led with the testLed0 function.
2019-12-03 Better convertion between rgb and spi code
2019-12-17 Addel eagle lib with headers for small nucleos
2020-01-07 Complete rewriting of files architecture
2020-01-07 New version of DAC board based on AD5391 chip
2020-01-07 new version of analog board based on L432
2020-01-07 New demo MIDI files
2020-01-07 new documentation
2020-01-07 config files
2020-01-07 new budget estimatino
2020-01-07 new version of serial debugger
2020-01-07 Now ignore Icon files (OS X)
2020-01-07 Deleted Icon (OS X)
2020-01-11 fixed bug in MidiInHandler when no input MIDI Keyboard available
2020-01-12 ignore .o and .su binaries
2020-01-12 checked connections
2020-01-12 Fixed numerous bugs with Midi CC processing ; should be fine now
2020-01-12 Removed binaries from tree
2020-01-12 Removed HAL binaries from tree
2020-01-12 now ignore .su files
2020-01-12 now ignore elf files
2020-01-12 added datasheet
2020-01-20 bug fix on LM13700 schematics
2020-01-20 Added new Midi CC to time constant conversion table for better parameter tweaking
2020-01-21 The drivers and other files regarding the interface are included
2020-01-21 Layout half way
2020-01-21 add VCO.java to RPI/src/view/touchscreen
2020-01-21 Cleanup of neopixel code and added eagle lib with Neopixel rings
2020-01-21 deleting test file
2020-01-21 bug fixes with Midi In
2020-01-22 version 1 nouveau pcb vcf
2020-01-24 Added LTSpice simulation for the MOOG ladder VCF
2020-01-24 Added utilities to debug Raspberry code
2020-01-25 Created new folder for main board
2020-01-25 Moved eagle files to new folder
2020-01-26 Added hack to fix wrong LED soldering bug
2020-01-26 Added Moog Ladder Filter complete simulation
2020-01-26 Moved filed to subfolder
2020-01-26 Changed listener method names
2020-01-26 Finalized frontpane hardware test
2020-01-26 Hardware test ok
2020-01-26 Simplified method names for event listeners
2020-01-28 Create PCB-Xbee-Rasberry
2020-02-03 Added bizarre-controle folder in eagle-schematics
2020-02-08 Correcting errors in neopixel code
2020-02-08 Created a board to host graph bars and buttons.
2020-02-08 Improved interface board
2020-02-19 Moved raspberry xbee shield eagle files to dedicated folder
2020-02-19 added LM13700 ltspice elements
2020-02-19 Bug fix regarding front pane
2020-02-19 edit
2020-02-24 Etage sortie VCF v4
2020-02-25 Logical errors in memory management are corrected. Furthermore, I am trying to ditch the uses of SPI to use GPIO instead. Since it is now too slow, I will try to increase the clock speed.
2020-02-26 Output_Stage_v4
2020-03-03 schematic fix
2020-03-03 Fixed file names
2020-03-03 Added new schematic for combined VCA and output OpAmp
2020-03-03 New VCF multifilter design
2020-03-03 new design for stm32 + analog board
2020-03-03 Deleted unused folder
2020-03-03 Added Mathematica transfer function calculation of LP/BP/HP VCF3320 design
2020-03-03 New LTSpice simulation of combined VCA 13700 + OpAmp output stage
2020-03-03 New Ladder filter based VCF design
2020-03-03 Pref update
2020-04-21 Finished ASM trasmition functions
2020-04-21 Updated PCB
2020-04-22 Improved STM32 F767 code architecture so as to better separate low- and high-level features
2020-04-22 Added new schematic for HP-LP-BP filter
2020-04-22 Complete transfer function calculation
2020-04-25 Added TIM2 IRQ support for AD5391 / MCP23017
2020-04-25 Removed binaries from github
2020-04-26 Merged code from F767, validated AD5391 and MCP23017 outputs
2020-04-26 Removed bin files
2020-05-01 Fixed bug related to EXTI spurious interrupts
2020-05-01 Added VCA and VCF enveloppes generation
2020-05-03 cleaned .gitignore files
2020-05-03 how do these fucking .project files work?
2020-05-04 Optimized code performance
2020-05-04 added MIDI in support
2020-05-04 Changed formatting of MIDI utility
2020-05-07 Improved midi support
2020-05-07 Added more options in properties.txt
2020-05-08 calibration support underway
2020-05-09 improved calibration
2020-05-26 Added new field OPEN_SYNTH_CTRLPANE_SIMULATION
2020-05-26 Updated calib figures
2020-05-26 Bug fix with 16+16 bit counter
2020-06-19 added midi device
2020-06-19 projet change
2020-06-19 new SMD main board bersion
2020-06-19 new SPICE simulation
2020-06-23 PCB for F446
2020-06-23 PCB update
2020-06-24 Added new F4 based implementation
2020-06-24 Final PCB version sent to eurocircuits.com
2020-10-26 Initial commit for STM32F446 Board v7 C code
2020-10-26 Java code is now fully functional
2020-10-26 fixed pol cap and LED orientation errors
2020-10-26 added debug utility
2020-10-26 changed name
2020-10-27 Updated net names
2020-11-10 Reorganized folders
2020-11-10 added doc
2020-11-10 added README files
2020-12-05 improved front pane v3
2020-12-10 Updated front pane
2020-12-13 Front pane update
2020-12-17 Finished front pane and sent to production
2021-10-09 renaming
2021-10-09 Create DESCRIPTION
2021-10-09 added graphism proposal
2021-12-29 added stm32cubeide extensions for ignored binaries
2021-12-29 New STM32CubeIDE project for frontpane board
2021-12-29 Renamed folder
2021-12-29 Stickers for easier debugging
2022-01-23 new front pane picture
2022-02-19 STM32CubeIDE version upgrade
2022-02-19 changed class architecture
2022-02-19 added new information
2022-02-19 enabled PullUp for EXTI inputs connected to MCP INT output
2022-02-19 renamed full-board-L432KC
2022-02-19 renamed folder and STM32CubeIDE project
2022-03-06 DIL to CMS adapter for the STLink v3 programmer
2022-03-06 no change
2022-03-06 bug fixes for encoder code
2022-05-10 Delete front-pane/eagle-schematics/v3/CAMOutputs directory
    can be regenerated on demand
2022-05-10 Delete adapter-STDC14-DIL.brd
    moved outside the project
2022-05-10 Delete adapter-STDC14-DIL.cam
    moved outside the project
2022-05-10 Delete adapter-STDC14-DIL.sch
    moved outside the project
2022-05-10 Renamed STM32CubeIDE project
2022-05-10 Added missing net label on BH2221 DAC
2022-05-10 STM32F446 CubeMX firmware upgrade
2022-05-10 Slight translation of touch screen
    This doesn't have any consequence on the electrical design
2022-05-10 added CAD files for Laser cutting
2022-05-10 renamed file
2022-05-10 Delete eagle-schematics directory
    empty folder
2022-09-02 new box cover design for Laser cutting machines
2022-09-02 comment added
2022-09-02 added annotations
2022-09-02 updated pin use
2022-09-02 pointing new errors on the board layout
2022-09-02 added enumeration for DAC channels
2022-09-02 deleted file - no MCP23017 on board
2022-09-02 deleted file
2022-09-02 lots of function renaming (C++ convention)
2022-09-02 mixer is a now object responsible for controlling VCA2164D
2022-09-02 not working yet
2022-09-02 this is a temporary 4 layer polyphonic version - work in progress
2022-09-02 updated HAL drivers to latest version
2022-09-03 MIDI receiving on USART1 is now ok
2022-09-03 added implementation of printf() via UART blocking call - DMA implementation pending
2022-09-03 disabled automatic generation of IRQ Handler by CubeIDE for USART1
2022-09-03 added UART1 related init'ing
2022-09-03 minor edits
2022-09-04 Edited TIM2 (input capture) parameters to match those of version L432KC
2022-09-04 added ZIP extension
2022-09-04 edited IRQ handler names
2022-11-04 Management of southern board encoders
    All eight MCP23017's are now handled correctly by software.
2022-11-04 Updated HAL firmware
2022-11-04 changed test procedure
2022-11-04 changed CIRCULAR to NORMAL for SPI3 + removed IRQ calls to HAL handlers
2022-11-04 HAL driver upgrade
2022-11-04 improved doc
2022-11-04 typos correction
2022-11-05 implemented alternate functions + led display now ok
2023-01-03 added support for alternate functions
